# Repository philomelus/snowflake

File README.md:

This is a schematic and PCB layout created with Kicad 5.1 for a snowflake with RGB LED's and wireless communication.

I have not had these PCB's manufactured, as I meant this as a hobby type thing and what I ended up with cost way more than I was willing to spend (the PCB is 6 layers, and even the cheap chinese pcb manufactures wanted several $100 USD to create the smallest batch).

As a result of the above, I do not know how many mistakes I've made, or whether these will even work.  This is my first wireless PCB, and while I followed all the advice and recommendations I could find, I cannot make any claim as to how well its done.  If you use it as a basis for your own project, just keep that in mind, and understand I make no claims as to whether it will work.

At some point, I'd like to refine the actual snowflak shape, as its pretty rough (I imported from an SVG created in Inkscape).  Also, it'd be nice to have multiple possible shapes rather than just the one, as well as different sizes (the default size is about 126mm (4.9in) by 132mm (5.2in)).  For its size, there are a LOT of LED's (32 per PCB!).  Partly I wanted to be able to have plenty of light points, but it also allows the LED's to be run at lower power and provide considerable amount of light and complex color saturations, making sparkling a real possibility.

Russ Gibson / November 2020

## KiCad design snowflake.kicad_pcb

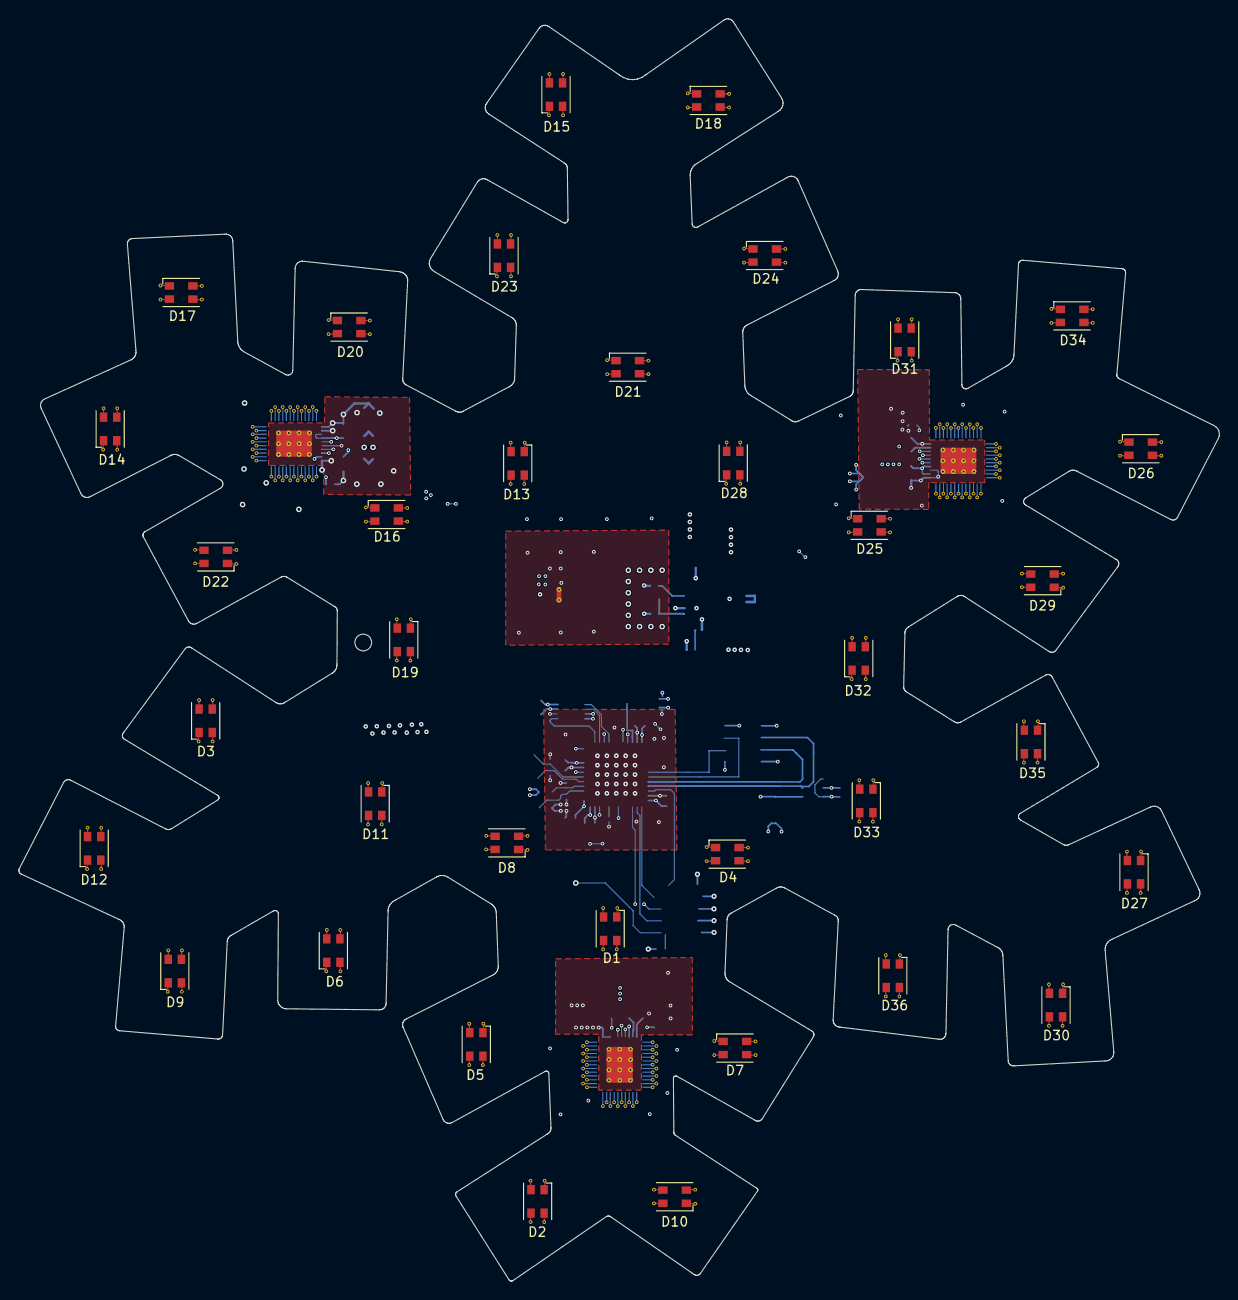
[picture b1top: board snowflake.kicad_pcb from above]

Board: 6 copper layers, 127.8 x 134.4 mm, 89 parts (0 on the bottom side), 149 nets.

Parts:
C1, C2: 10uF; C_1210
C3: 47uF; C_1210
C4: 22uF; C_0603
C5: 10uF; C_0603
C6, C10, C11, C15, C16, C20, C31: 1uF; C_0603
C7, C8, C12, C13, C17, C18: 10uF; CP_Elec_3x5.3
C9, C19: 100nF; C_0402_1005Metric
C14: 150uF; C_1210_3225Metric
C21: 4.7uF; CP_Elec_3x5.3
C22, C23: 9pF; R_0201
C24, C25: 8pF; R_0201
C26, C27, C28, C29, C30: 100nF; C_0402
D1, D2, D3, D4, D5, D6, D7, D8, D9, D10, D11, D12, D13, D14, D15, D16, D17, D18, D19, D20, D21, D22, D23, D24, D25, D26, D27, D28, D29, D30, D31, D32, D33, D34, D35, D36: LED_RABG; LED-RGB-RABG-Via's
J1: 2.1mm Jack; RASM722PX
J2: ARM-JTAG-SWD-10; Pin_Header_Straight_2x05_Pitch1.27mm_SMD
J3: 2x4-1.27mm-0.05in; PinHeader_2x04_P1.27mm_Vertical_SMD_CCW
L1: 2.2uH; Inductor-Vishay-IHLP-1212BZ
R1: 40.2k; R_0402
R2: 4.42k; R_0402
R3: 10k; R_0201
R4: 1.37k; R_0402
R5, R6, R7: 3.65K; R_0402
R11: 10K; R_0201
U1: TPSM84424; TPSM84624MOLR
U2: TPS62291; WSON-6-1EP_2x2mm_P0.65mm_EP1x1.6mm_ThermalVias
U3, U4, U5: LP5036; VQFN-46-1EP_5x6mm_P0.4mm_EP2.8x3.8mm_ThermalVias_LEDVias
U6: STM32F413CHUx; QFN-48-1EP_7x7mm_P0.5mm_EP5.6x5.6mm
U7: M95512; TDFN-8-1EP_3x2mm_P0.5mm_EP1.80x1.65mm
U8: TPD3S014; SOT-23-6
Y1: 32.768K; Crystal_SMD_Epson_FC135R-2pin_3.2x1.5mm
Y2: 16Mhz; Crystal_SMD_Epson_FA20H-4pin_2.5x2.0mm

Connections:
+3V3: C5.1, C26.1, C27.1, C28.1, C29.1, C30.1, C31.1, J2.1, J3.8, L1.2, U2.3, U6.1, U6.9, U6.24, U6.36, U6.48, U7.3, U7.7, U7.8
+5V: C3.1, C4.1, C7.1, C8.1, C9.1, C10.1, C12.1, C13.1, C15.1, C17.1, C18.1, C20.1, D1.2, D2.2, D3.2, D4.2, D5.2, D6.2, D7.2, D8.2, D9.2, D10.2, D11.2, D12.2, D13.2, D14.2, D15.2, D16.2, D17.2, D18.2, D19.2, D20.2, D21.2, D22.2, D23.2, D24.2, D25.2, D26.2, D27.2, D28.2, D29.2, D30.2, D31.2, D32.2, D33.2, D34.2, D35.2, D36.2, R3.1, U1.1, U1.8, U2.2, U2.4, U2.5, U3.40, U4.39, U4.40, U5.38, U5.40, U8.1, U8.3
/+5V Supply/+12V: C1.1, C2.1, J1.3, U1.11, U1.22
/+5V Supply/AGND: R1.2, R2.2, R4.2, U1.3, U1.9, U1.23
/MCU/BOOT: R11.2, U6.44
/MCU/DBG_RX: J3.7, U6.31
/MCU/DBG_TX: J3.6, U6.30
/MCU/HSE_IN: C24.1, U6.3, Y2.1
/MCU/HSE_OUT: C25.1, U6.4, Y2.3
/MCU/LSE_IN: C22.1, U6.5, Y1.1
/MCU/LSE_OUT: C23.1, U6.6, Y1.2
/MCU/MCK-CFG: U6.15, U7.6
/MCU/MCS-CFG: U6.14, U7.1
/MCU/MISO-CFG: U6.17, U7.5
/MCU/MOSI-CFG: U6.16, U7.2
/MCU/RESET: C19.1, J2.10, U6.7
/MCU/SWCLK-TCK: J2.4, U6.37
/MCU/SWDIO-TMS: J2.2, U6.34
/MCU/TDI: J2.8, U6.38
/MCU/TDO-SWO: J2.6, U6.39
/MCU/USB-D+: J3.2, U6.33, U8.5
/MCU/USB-D-: J3.3, U6.32, U8.6
/MCU/VBUS: C14.1, J3.1, U8.4
/MCU/VCAP: C21.1, U6.22
/SCL: U3.42, U4.42, U5.42, U6.21
/SDA: U3.41, U4.41, U5.41, U6.46
/SEN-LED-1: U3.43, U6.42
/SEN-LED-2: U5.43, U6.20
/SEN-LED-3: U4.43, U6.12
GND: C1.2, C2.2, C3.2, C4.2, C5.2, C6.2, C7.2, C8.2, C9.2, C10.2, C11.2, C12.2, C13.2, C14.2, C15.2, C16.2, C17.2, C18.2, C19.2, C20.2, C21.2, C22.2, C23.2, C24.2, C25.2, C26.2, C27.2, C28.2, C29.2, C30.2, C31.2, J1.1, J2.3, J2.5, J2.7, J2.9, J3.4, J3.5, R5.2, R6.2, R7.2, R11.1, U1.12, U1.13, U1.14, U1.15, U1.18, U1.19, U1.20, U1.21, U2.6, U2.7, U3.37, U3.38, U3.39, U3.46, U3.47, U4.37, U4.38, U4.46, U4.47, U5.37, U5.39, U5.46, U5.47, U6.8, U6.23, U6.35, U6.47, U6.49, U7.4, U8.2, Y2.2, Y2.4
unnamed: C6.1, U3.45
unnamed: C11.1, U4.45
unnamed: C16.1, U5.45
unnamed: D1.1, U3.1
unnamed: D1.3, U3.3
unnamed: D1.4, U3.2
unnamed: D2.1, U3.13
unnamed: D2.3, U3.15
unnamed: D2.4, U3.14
unnamed: D3.1, U3.25
unnamed: D3.3, U3.27
unnamed: D3.4, U3.26
unnamed: D4.1, U3.4
unnamed: D4.3, U3.6
unnamed: D4.4, U3.5
unnamed: D5.1, U3.16
unnamed: D5.3, U3.18
unnamed: D5.4, U3.17
unnamed: D6.1, U3.28
unnamed: D6.3, U3.30
unnamed: D6.4, U3.29
unnamed: D7.1, U3.7
unnamed: D7.3, U3.9
unnamed: D7.4, U3.8
unnamed: D8.1, U3.19
unnamed: D8.3, U3.21
unnamed: D8.4, U3.20
unnamed: D9.1, U3.31
unnamed: D9.3, U3.33
unnamed: D9.4, U3.32
unnamed: D10.1, U3.10
unnamed: D10.3, U3.12
unnamed: D10.4, U3.11
unnamed: D11.1, U3.22
unnamed: D11.3, U3.24
unnamed: D11.4, U3.23
unnamed: D12.1, U3.34
unnamed: D12.3, U3.36
unnamed: D12.4, U3.35
unnamed: D13.1, U4.1
unnamed: D13.3, U4.3
unnamed: D13.4, U4.2
unnamed: D14.1, U4.13
unnamed: D14.3, U4.15
unnamed: D14.4, U4.14
unnamed: D15.1, U4.25
unnamed: D15.3, U4.27
unnamed: D15.4, U4.26
unnamed: D16.1, U4.4
unnamed: D16.3, U4.6
unnamed: D16.4, U4.5
unnamed: D17.1, U4.16
unnamed: D17.3, U4.18
unnamed: D17.4, U4.17
unnamed: D18.1, U4.28
unnamed: D18.3, U4.30
unnamed: D18.4, U4.29
unnamed: D19.1, U4.7
unnamed: D19.3, U4.9
unnamed: D19.4, U4.8
unnamed: D20.1, U4.19
unnamed: D20.3, U4.21
unnamed: D20.4, U4.20
unnamed: D21.1, U4.31
unnamed: D21.3, U4.33
unnamed: D21.4, U4.32
unnamed: D22.1, U4.10
unnamed: D22.3, U4.12
unnamed: D22.4, U4.11
unnamed: D23.1, U4.22
unnamed: D23.3, U4.24
unnamed: D23.4, U4.23
unnamed: D24.1, U4.34
unnamed: D24.3, U4.36
unnamed: D24.4, U4.35
unnamed: D25.1, U5.1
unnamed: D25.3, U5.3
unnamed: D25.4, U5.2
unnamed: D26.1, U5.13
unnamed: D26.3, U5.15
unnamed: D26.4, U5.14
unnamed: D27.1, U5.25
unnamed: D27.3, U5.27
unnamed: D27.4, U5.26
unnamed: D28.1, U5.4
unnamed: D28.3, U5.6
unnamed: D28.4, U5.5
unnamed: D29.1, U5.16
unnamed: D29.3, U5.18
unnamed: D29.4, U5.17
unnamed: D30.1, U5.28
unnamed: D30.3, U5.30
unnamed: D30.4, U5.29
unnamed: D31.1, U5.7
unnamed: D31.3, U5.9
unnamed: D31.4, U5.8
unnamed: D32.1, U5.19
unnamed: D32.3, U5.21
unnamed: D32.4, U5.20
unnamed: D33.1, U5.31
unnamed: D33.3, U5.33
unnamed: D33.4, U5.32
unnamed: D34.1, U5.10
unnamed: D34.3, U5.12
unnamed: D34.4, U5.11
unnamed: D35.1, U5.22
unnamed: D35.3, U5.24
unnamed: D35.4, U5.23
unnamed: D36.1, U5.34
unnamed: D36.3, U5.36
unnamed: D36.4, U5.35
unnamed: L1.1, U2.1
unnamed: R1.1, U1.24
unnamed: R2.1, U1.5
unnamed: R3.2, R4.1, U1.2
unnamed: R5.1, U3.44
unnamed: R6.1, U4.44
unnamed: R7.1, U5.44
unnamed: U1.16, U1.17

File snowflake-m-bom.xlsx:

Reference | Quantity | Value | Description | Footprint | OEM | Part No.
C1 C2 | 2 | 10uF | CER 10UF 50V X5R 1210 | SMD 1210 | TDK | C3225X5R1H106K250AB
C10 C6 C15 C11 C20 C16 C31 | 7 | 1uF | CER 1UF 10V X5R 0603 | SMD 0603 | Kemet | C0603C105K8PACTU
C14 | 1 | 150uF |  | SMD 1210 | Kemet | C1210C107M4PAC7800
C21 | 1 | 4.7uF | ALUM 4.7UF 20% 25V SMD | SMD 3mm x 5.3mm | Nichicon | UWT1E4R7MCL2GB
C23 C22 | 2 | 9pF | CER 9PF 25V C0G/NP0 0201 | SMD 0201 | Kemet | CBR02C909B3GAC
C24 C25 | 2 | 8pF | CER 8PF 25V C0G/NP0 0201 | SMD 0201 | Kemet | CBR02C809B3GAC
C28 C29 C30 C27 C26 | 5 | 100nF | CER 0.1UF 16V X7R 0402 | SMD 0402 | Kemet | C0402C104K4RACAUTO
C3 | 1 | 47uF | CER 47UF 16V X5R 1210 | SMD 1210 | Murata Electronics | GRM32ER61C476KE15L
C4 | 1 | 22uF | CER 22UF 6.3V X5R 0603 | SMD 0603 | Murata Electronics | GRM188R60J226MEA0D
C5 | 1 | 10uF | CER 10UF 6.3V X5R 0603 | SMD 0603 | Kemet | C0603C106M9PACTU
C8 C7 C13 C12 C18 C17 | 6 | 10uF | ALUM 10UF 20% 16V SMD | SMD 3mm x 5.3mm | Nichicon | UWT1C100MCL2GB
C9 C19 | 2 | 100nF | CER 0.1UF 16V X7R 0402 | SMD 0402 | Kemet | C0402C104K4RACAUTO
D1 D4 D10 D2 D5 D8 D11 D3 D6 D9 D12 D7 D13 D16 D22 D14 D17 D20 D23 D15 D18 D21 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 | 36 | RGB |  | PLCC-4
J1 | 1 | 2.1mm Jack | Conn Power PL 2 POS Solder RA SMD 3 Terminal 1 Port | Custom | Switchcraft | RASM722PX
J2 | 1 | ARM JTAG Header | Header SMD 10POS 1.27MM | Header 2x5 @ 1.27mm SMD | Samtec Inc. | FTS-105-01-F-DV-P-TR
J3 | 1 | Header | Header SMD 8POS 1.27MM | Header 2x4 @ 1.27mm SMD | Samtec Inc. | FTS-104-01-F-DV-P-TR
L1 | 1 | 2.2uH | IND 2.2UH 3A 46 MOHM SMD | IHLP-1212BZ | Vishay-Dale | IHLP1212BZER2R2M11
R1 | 1 | 40.2k | SMD 40.2K OHM 1% 1/16W 0402 | SMD 0402 | Vishay-Dale | CRCW040240K2FKEDC
R11 | 1 | 10K | SMD 10K OHM 1% 1/20W 0201 | SMD 0201 | Yageo | RC0201FR-0710KL
R2 | 1 | 4.42k | SMD 4.42K OHM 1% 1/16W 0402 | SMD 0402 | Vishay-Dale | CRCW04024K42FKED
R3 | 1 | 10k | SMD 10K OHM 1% 1/20W 0201 | SMD 0201 | Yageo | RC0201FR-0710KL
R4 | 1 | 1.37k | SMD 1.37K OHM 1% 1/16W 0402 | SMD 0402 | Vishay-Dale | CRCW04021K37FKED
R5 R6 R7 | 3 | 3.65K | SMD 3.65KOHM 0.1% 1/16W 0402 | SMD 0402 | Yageo | RT0402BRD073K65L
U1 | 1 | TPSM84424 | Module DC DC Converter 1 Output 0.6 ~ 10V 4A 4.5V - 17V Input | QFM-24 | Texas Instruments | TPSM84424MOLR
U2 | 1 | TPS62291 | REG BUCK 3.3V 1A | WSON-6 2mm x 2mm @ 0.65mm | Texas Instruments | TPS62291DRVR
U3 U4 U5 | 3 | LP5036 | LED RGB Driver IC 12 (36) Output Linear Dimming | VQFN-46 5mm x 6mm @ 0.4mm | Texas Instruments | LP5036RJVR
U6 | 1 | STM32F413CHUx | MCU | QFN-48 7mm x 7mm_@ 0.5mm | STElectronics | STM32F413CHU6
U7 | 1 | M95512 | EEPROM 512K SPI | TDFN-8 3mm x 2mm @ 0.5mm | STElectronics | M95512-DFMC6TG
U8 | 1 | TPD3S014 | TVS DIODE 6SOT | SOT-23-6 | Texas Instruments | TPD3S014DBVR
Y1 | 1 | 32.768K | CRYSTAL 32.7680KHZ 9.0PF SMT | Epson FC135R-2pin 3.2mm x 1.5mm | Epson | FC-135R 32.7680KF-AC3
Y2 | 1 | 16Mhz | CRYSTAL 16.0000MHZ 8PF SMD | Epson FA20H-4pin 2.5mm x 2.0mm | Epson | FA-20H 16.0000MF10Z-AJ0

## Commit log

2020-01-12 Initial import.
2020-01-12 File structure cleanup.
2020-01-16 Merged usb and debug to single 1.27mm header.
2020-01-16 More assembly updates; Nothing major.
2020-01-20 Update gitignore.
2020-11-19 Final changes. Its beedn a few months, so I do not remember exactly, but diffs show enough changes to make it worth keeping the revisions. Everything *looks* ok.
2020-11-19 Removed generated BOM files (pdf, xlsx) from git.
2020-11-19 Added license.
2020-11-19 Removed (missed) BOM csv.
2020-11-19 Fixed typo in readme.
2020-11-19 Removed archives and docs for used components, etc.
